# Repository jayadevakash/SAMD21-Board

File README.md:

# SAMD21-Board
Development Board Powered by SAMD21 Micro-controller. Project Credit: IoT Hive

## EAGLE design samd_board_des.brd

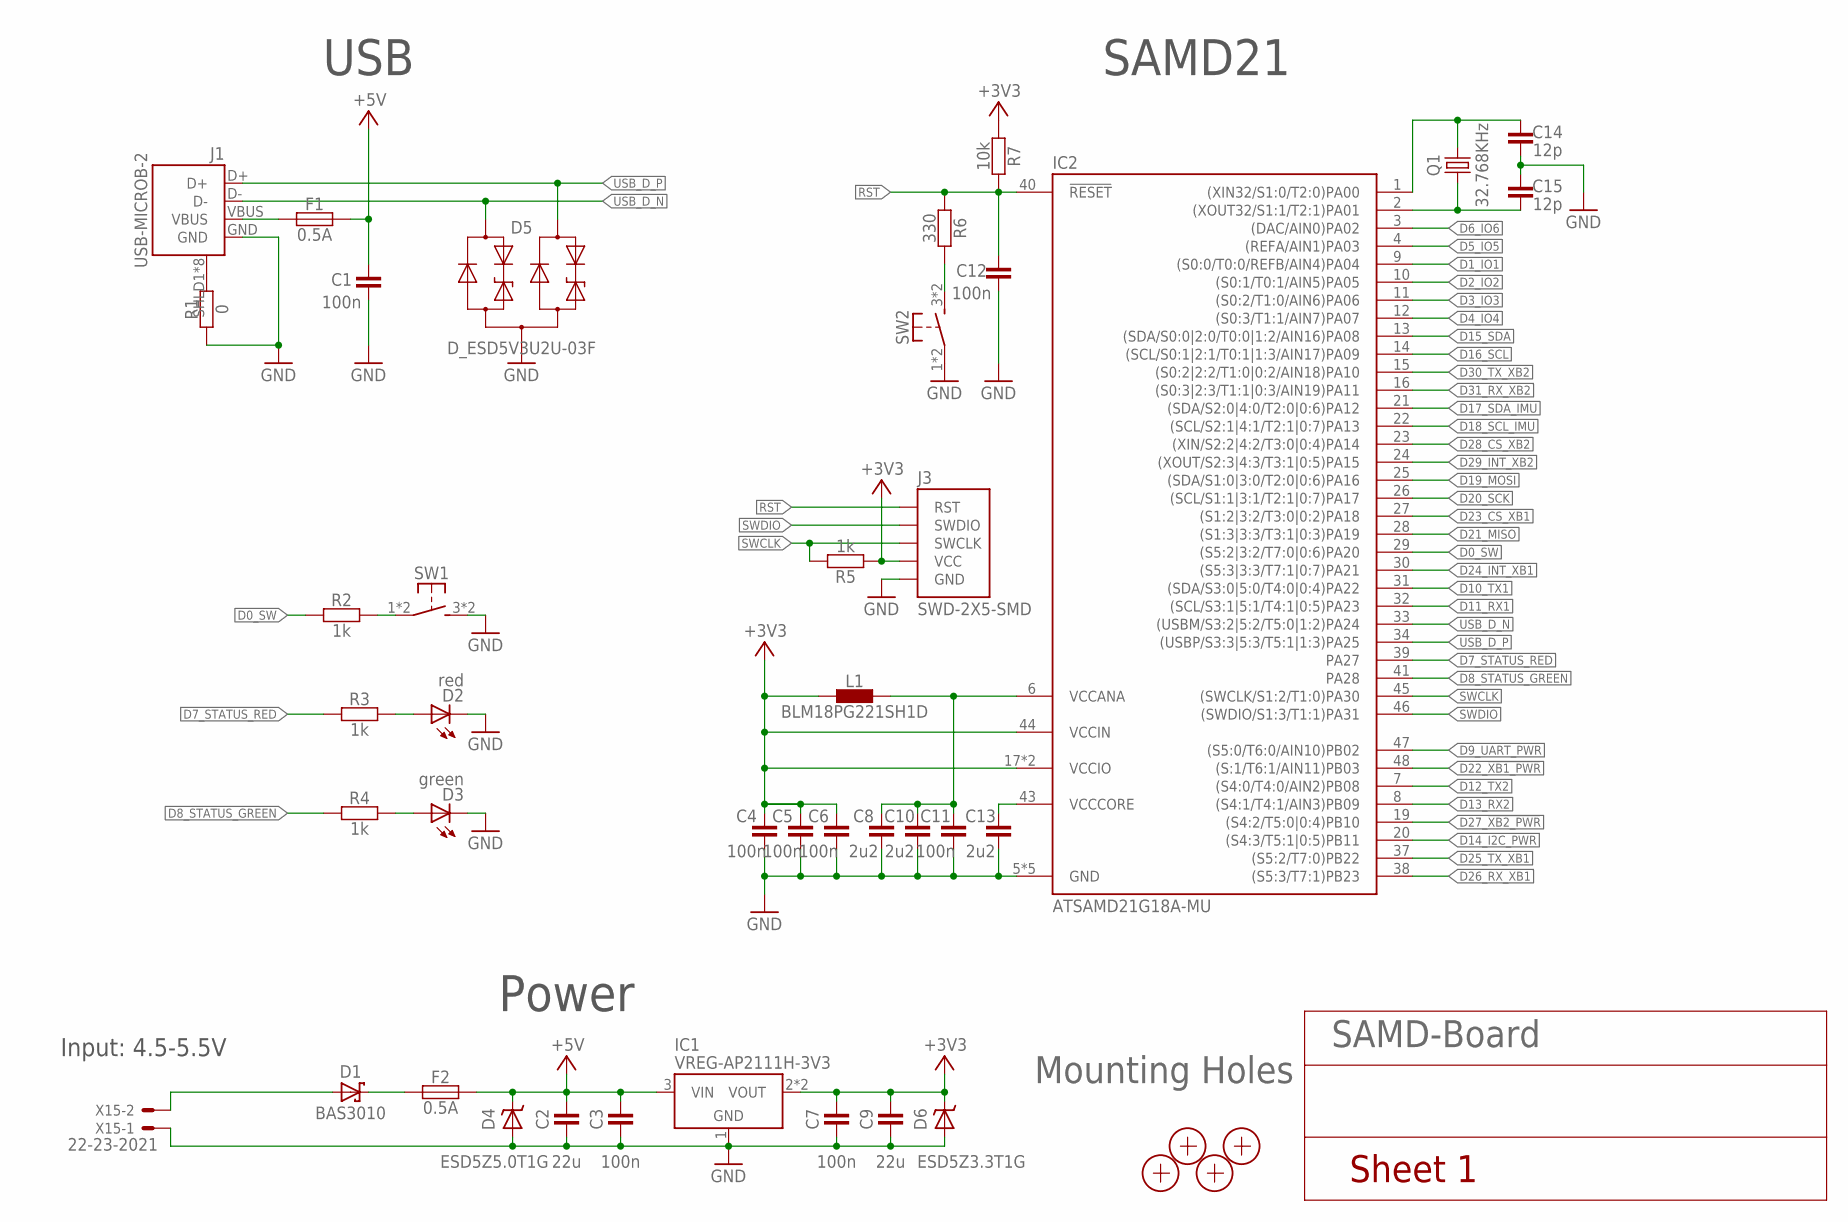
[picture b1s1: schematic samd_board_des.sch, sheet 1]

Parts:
C1, C3, C4, C5, C6, C7, C11, C12: 100n; C0402
C2, C9: 22u; C0805
C8, C10, C13: 2u2; C0402
C14, C15: 12p; C0402
D1: BAS3010; SOD323
D2: red; C0603
D3: green; C0603
D4: ESD5Z5.0T1G; SOD523
D5: D_ESD5V3U2U-03F; SOT723
D6: ESD5Z3.3T1G; SOD523
F1, F2: 0.5A; C0805
IC1: VREG-AP2111H-3V3; SOT223
IC2: ATSAMD21G18A-MU; QFN48-PAD
J1: USB-MICROB-2; USB-MICROB-10118194
J3: SWD-2X5-SMD; SWD-2X5_SMD
L1: BLM18PG221SH1D; C0603
Q1: 32.768KHz; CRYSTAL_ZM315
R1: 0; C0402
R2, R3, R4, R5: 1k; C0402
R6: 330; C0402
R7: 10k; C0402
SW1: PTS645SH50SMTR92-Grey; SW6X6_SMD
SW2: PTS645SK50SMTR92-Red; SW6X6_SMD
X1, X2, X3, X4: PASSER-07; PASSER_07MM
X15: 22-23-2021

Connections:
+3V3: C4.2, C5.2, C6.2, C7.2, C9.2, D6.C, IC1.2 (VOUT), IC1.4 (VOUT), IC2.17 (VCCIO), IC2.36 (VCCIO), IC2.44 (VCCIN), J3.VCC, L1.1, R5.1, R7.1; also elsewhere on the board
+5V: C1.2, C2.2, C3.2, D4.C, F1.2, F2.2, IC1.3 (VIN); also elsewhere on the board
D0_SW: IC2.29 ((S5:2|3:2/T7:0|0:6)PA20), R2.1
D1_IO1: IC2.9 ((S0:0/T0:0/REFB/AIN4)PA04); also elsewhere on the board
D2_IO2: IC2.10 ((S0:1/T0:1/AIN5)PA05); also elsewhere on the board
D3_IO3: IC2.11 ((S0:2/T1:0/AIN6)PA06); also elsewhere on the board
D4_IO4: IC2.12 ((S0:3/T1:1/AIN7)PA07); also elsewhere on the board
D5_IO5: IC2.4 ((REFA/AIN1)PA03); also elsewhere on the board
D6_IO6: IC2.3 ((DAC/AIN0)PA02); also elsewhere on the board
D7_STATUS_RED: IC2.39 (PA27), R3.1
D8_STATUS_GREEN: IC2.41 (PA28), R4.1
D9_UART_PWR: IC2.47 ((S5:0/T6:0/AIN10)PB02); also elsewhere on the board
D10_TX1: IC2.31 ((SDA/S3:0|5:0/T4:0|0:4)PA22); also elsewhere on the board
D11_RX1: IC2.32 ((SCL/S3:1|5:1/T4:1|0:5)PA23); also elsewhere on the board
D12_TX2: IC2.7 ((S4:0/T4:0/AIN2)PB08); also elsewhere on the board
D13_RX2: IC2.8 ((S4:1/T4:1/AIN3)PB09); also elsewhere on the board
D14_I2C_PWR: IC2.20 ((S4:3/T5:1|0:5)PB11); also elsewhere on the board
D15_SDA: IC2.13 ((SDA/S0:0|2:0/T0:0|1:2/AIN16)PA08); also elsewhere on the board
D16_SCL: IC2.14 ((SCL/S0:1|2:1/T0:1|1:3/AIN17)PA09); also elsewhere on the board
D17_SDA_IMU: IC2.21 ((SDA/S2:0|4:0/T2:0|0:6)PA12); also elsewhere on the board
D18_SCL_IMU: IC2.22 ((SCL/S2:1|4:1/T2:1|0:7)PA13); also elsewhere on the board
D19_MOSI: IC2.25 ((SDA/S1:0|3:0/T2:0|0:6)PA16); also elsewhere on the board
D20_SCK: IC2.26 ((SCL/S1:1|3:1/T2:1|0:7)PA17); also elsewhere on the board
D21_MISO: IC2.28 ((S1:3|3:3/T3:1|0:3)PA19); also elsewhere on the board
D22_!XB1_PWR: IC2.48 ((S:1/T6:1/AIN11)PB03); also elsewhere on the board
D23_CS_XB1: IC2.27 ((S1:2|3:2/T3:0|0:2)PA18); also elsewhere on the board
D24_INT_XB1: IC2.30 ((S5:3|3:3/T7:1|0:7)PA21); also elsewhere on the board
D25_TX_XB1: IC2.37 ((S5:2/T7:0)PB22); also elsewhere on the board
D26_RX_XB1: IC2.38 ((S5:3/T7:1)PB23); also elsewhere on the board
D27_!XB2_PWR: IC2.19 ((S4:2/T5:0|0:4)PB10); also elsewhere on the board
D28_CS_XB2: IC2.23 ((XIN/S2:2|4:2/T3:0|0:4)PA14); also elsewhere on the board
D29_INT_XB2: IC2.24 ((XOUT/S2:3|4:3/T3:1|0:5)PA15); also elsewhere on the board
D30_TX_XB2: IC2.15 ((S0:2|2:2/T1:0|0:2/AIN18)PA10); also elsewhere on the board
D31_RX_XB2: IC2.16 ((S0:3|2:3/T1:1|0:3/AIN19)PA11); also elsewhere on the board
GND: C1.1, C2.1, C3.1, C4.1, C5.1, C6.1, C7.1, C8.1, C9.1, C10.1, C11.1, C12.1, C13.1, C14.2, C15.1, D2.C, D3.C, D4.A, D5.3 (A), D6.A, IC1.1 (GND), IC2.5 (GND), IC2.18 (GND), IC2.35 (GND), IC2.42 (GND), IC2.TP (GND), J1.GND, J3.GND@1 (GND), J3.GND@2 (GND), J3.GND@3 (GND), R1.1, SW1.3 (S1), SW1.4 (S1), SW2.1, SW2.2 (P1), X15.1; also elsewhere on the board
unnamed: C14.1, IC2.1 ((XIN32/S1:0/T2:0)PA00), Q1.2
unnamed: C15.2, IC2.2 ((XOUT32/S1:1/T2:1)PA01), Q1.1
unnamed: D2.A, R3.2
unnamed: D3.A, R4.2
unnamed: R6.2, SW2.3 (S1), SW2.4 (S1)
RST: C12.2, IC2.40 (!RESET), J3.RST, R6.1, R7.2
SHLD: J1.SHLD1 (SHIELD), J1.SHLD2 (SHIELD), J1.SHLD3 (SHIELD), J1.SHLD4 (SHIELD), J1.SHLD5 (SHIELD), J1.SHLD6 (SHIELD), J1.SHLD7 (SHIELD), J1.SHLD8 (SHIELD), R1.2
SW: R2.2, SW1.1, SW1.2 (P1)
SWCLK: IC2.45 ((SWCLK/S1:2/T1:0)PA30), J3.SWCLK, R5.2
SWDIO: IC2.46 ((SWDIO/S1:3/T1:1)PA31), J3.SWDIO
USB_D_N: D5.1 (C1), IC2.33 ((USBM/S3:2|5:2/T5:0|1:2)PA24), J1.D-
USB_D_P: D5.2 (C2), IC2.34 ((USBP/S3:3|5:3/T5:1|1:3)PA25), J1.D+
V5V: D1.C, F2.1
VBUS: F1.1, J1.VBUS
VCCANA: C8.2, C10.2, C11.2, IC2.6 (VCCANA), L1.2
VCCCORE: C13.2, IC2.43 (VCCCORE)
VIN: D1.A, X15.2

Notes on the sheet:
USB
SAMD21
Power
Input: 4.5-5.5V
SAMD-Board
Sheet 1
Mounting Holes

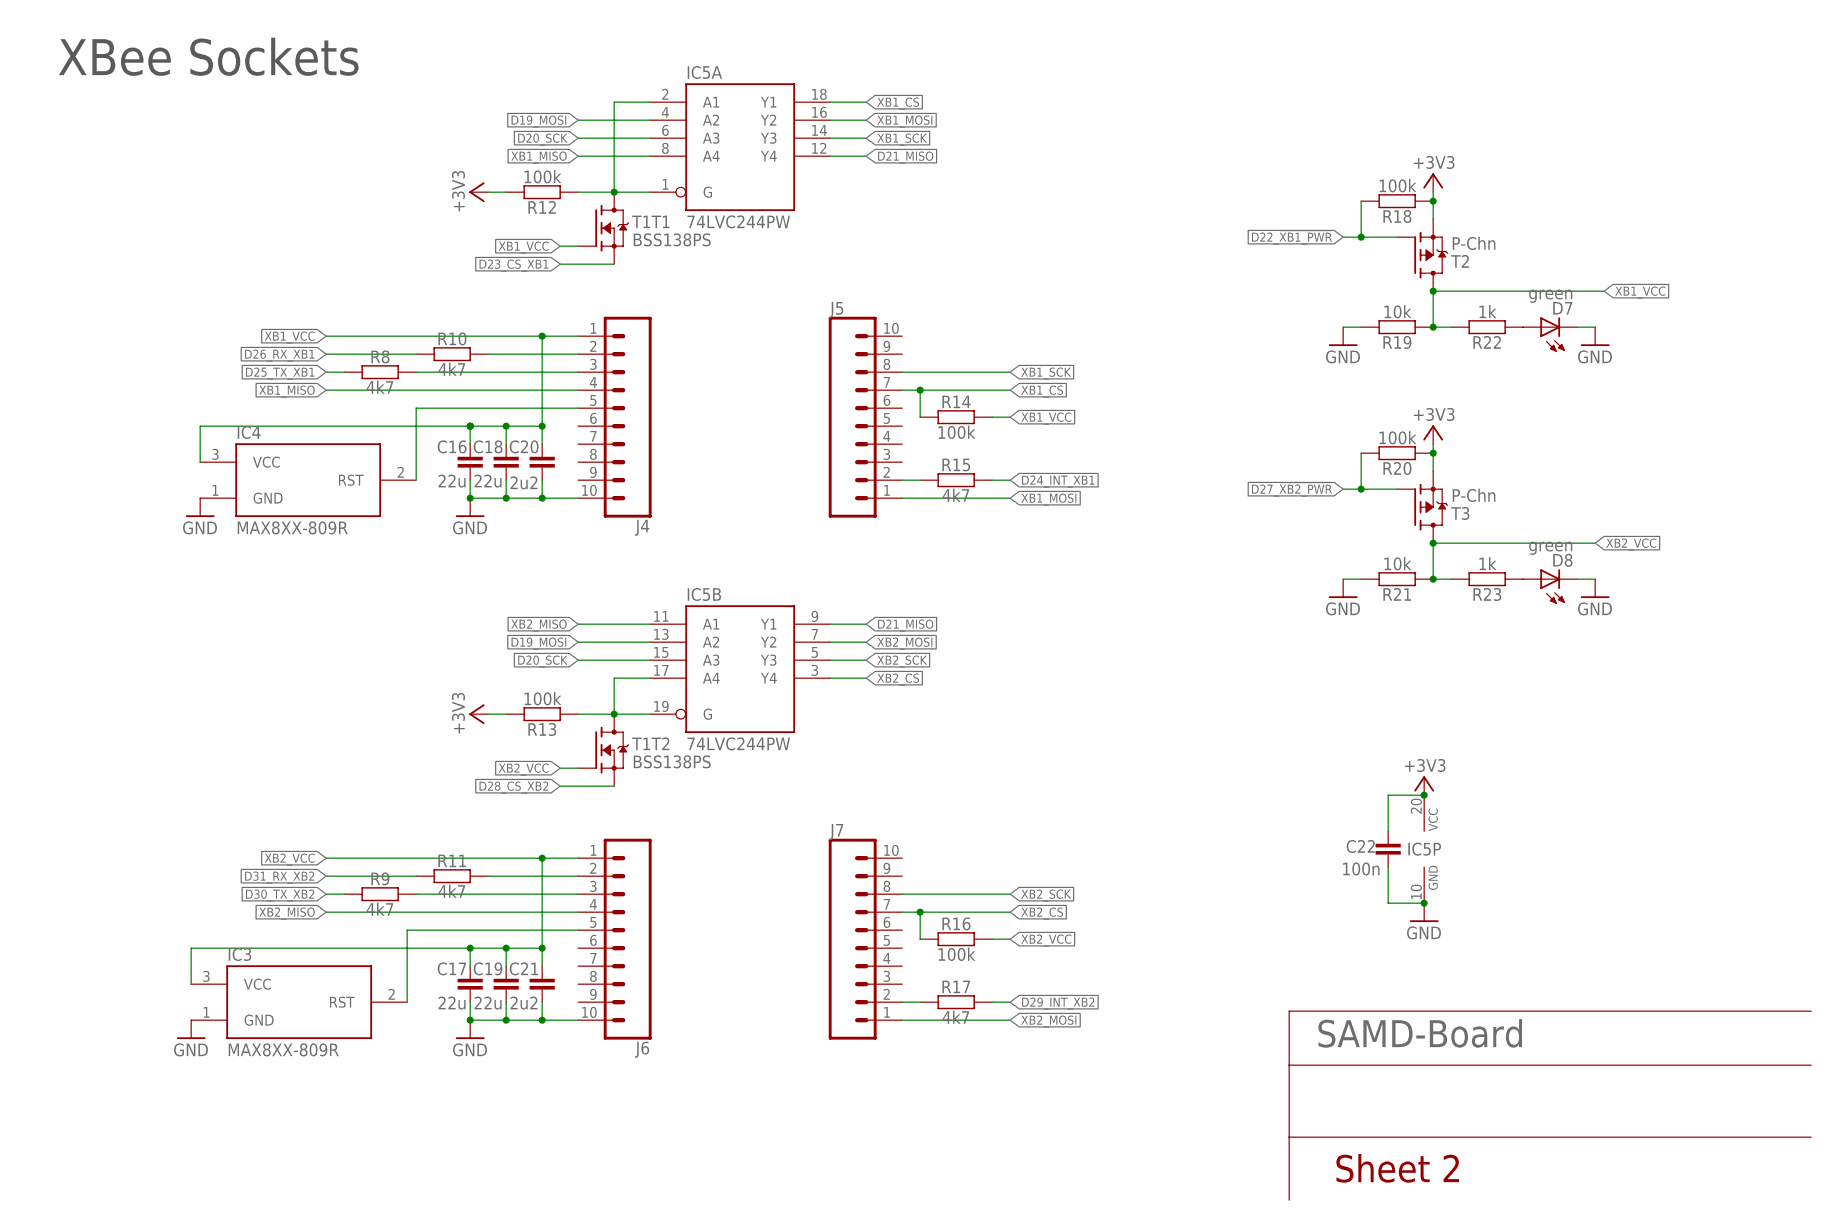
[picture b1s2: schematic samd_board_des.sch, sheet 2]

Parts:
C16, C17, C18, C19: 22u; C0805
C20, C21: 2u2; C0402
C22: 100n; C0402
D7, D8: green; C0603
IC3, IC4: MAX8XX-809R; SOT23
IC5: 74LVC244PW; TSSOP20
J4, J5, J6, J7: CONN_102MM; 1X10-2MM
R8, R9, R10, R11, R15, R17: 4k7; C0402
R12, R13, R14, R16, R18, R20: 100k; C0402
R19, R21: 10k; C0402
R22, R23: 1k; C0402
T1: BSS138PS; SOT363
T2, T3: P-Chn; SOT23

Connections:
+3V3: C22.2, IC5.20 (VCC), R12.2, R13.2, R18.1, R20.1, T2.2 (S), T3.2 (S); also elsewhere on the board
D19_MOSI: IC5.4 (A2), IC5.13 (A2); also elsewhere on the board
D20_SCK: IC5.6 (A3), IC5.15 (A3); also elsewhere on the board
D21_MISO: IC5.9 (Y1), IC5.12 (Y4); also elsewhere on the board
D22_!XB1_PWR: R18.2, T2.1 (G); also elsewhere on the board
D23_CS_XB1: T1.1 (S); also elsewhere on the board
D24_INT_XB1: R15.2; also elsewhere on the board
D25_TX_XB1: R8.1; also elsewhere on the board
D26_RX_XB1: R10.1; also elsewhere on the board
D27_!XB2_PWR: R20.2, T3.1 (G); also elsewhere on the board
D28_CS_XB2: T1.4 (S); also elsewhere on the board
D29_INT_XB2: R17.2; also elsewhere on the board
D30_TX_XB2: R9.1; also elsewhere on the board
D31_RX_XB2: R11.1; also elsewhere on the board
GND: C16.1, C17.1, C18.1, C19.1, C20.1, C21.1, C22.1, D7.C, D8.C, IC3.1 (GND), IC4.1 (GND), IC5.10 (GND), J4.10, J6.10, R19.2, R21.2; also elsewhere on the board
MCU_CS_XBEE1: IC5.1 (G), IC5.2 (A1), R12.1, T1.6 (D)
MCU_CS_XBEE2: IC5.17 (A4), IC5.19 (G), R13.1, T1.3 (D)
unnamed: D7.A, R22.1
unnamed: D8.A, R23.1
RST_XB1: IC4.2 (RST), J4.5
RST_XB2: IC3.2 (RST), J6.5
XB1_CS: IC5.18 (Y1), J5.7, R14.1
XB1_MISO: IC5.8 (A4), J4.4
XB1_MOSI: IC5.16 (Y2), J5.1
XB1_RX: J4.3, R8.2
XB1_SCK: IC5.14 (Y3), J5.8
XB1_TX: J4.2, R10.2
XB1_VCC: C16.2, C18.2, C20.2, IC4.3 (VCC), J4.1, R14.2, R19.1, R22.2, T1.2 (G), T2.3 (D)
XB2_CS: IC5.3 (Y4), J7.7, R16.1
XB2_MISO: IC5.11 (A1), J6.4
XB2_MOSI: IC5.7 (Y2), J7.1
XB2_RX: J6.3, R9.2
XB2_SCK: IC5.5 (Y3), J7.8
XB2_TX: J6.2, R11.2
XB2_VCC: C17.2, C19.2, C21.2, IC3.3 (VCC), J6.1, R16.2, R21.1, R23.2, T1.5 (G), T3.3 (D)
XBEE1_CTS/IRQ: J5.2, R15.1
XBEE2_CTS/IRQ: J7.2, R17.1

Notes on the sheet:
XBee Sockets
SAMD-Board
Sheet 2

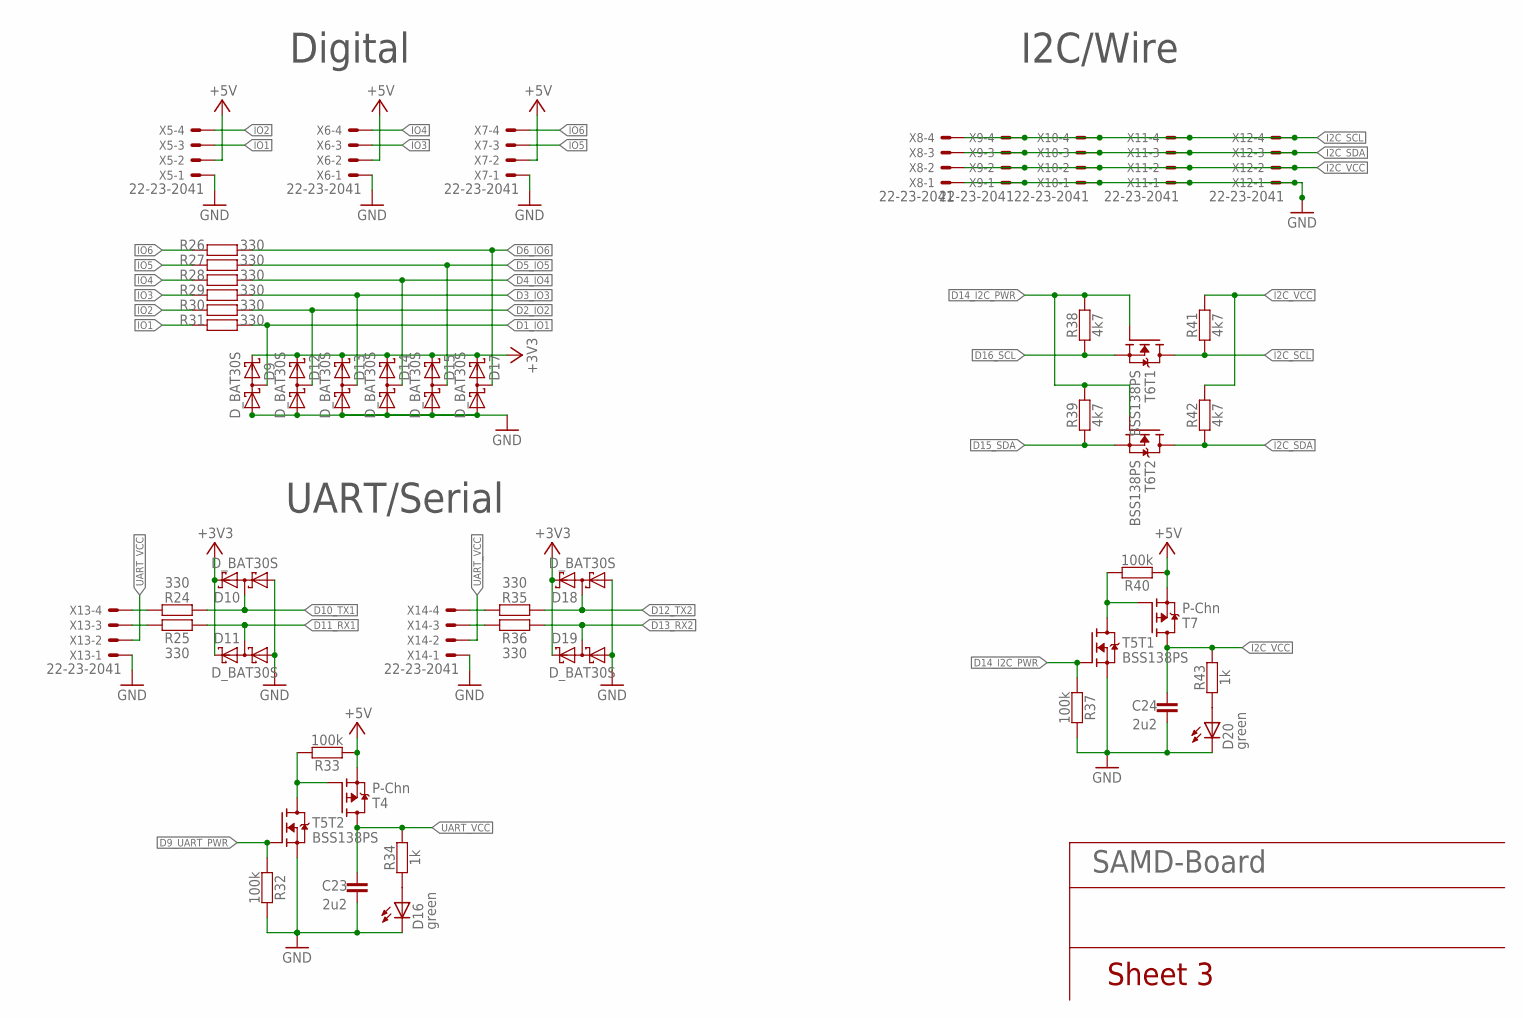
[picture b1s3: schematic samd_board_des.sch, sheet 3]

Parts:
C23, C24: 2u2; C0402
D9, D10, D11, D12, D13, D14, D15, D17, D18, D19: D_BAT30S; SOT323
D16, D20: green; C0603
R24, R25, R26, R27, R28, R29, R30, R31, R35, R36: 330; C0402
R32, R33, R37, R40: 100k; C0402
R34, R43: 1k; C0402
R38, R39, R41, R42: 4k7; C0402
T4, T7: P-Chn; SOT23
T5, T6: BSS138PS; SOT363
X5, X6, X7, X8, X9, X10, X11, X12, X13, X14: 22-23-2041

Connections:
!I2C_POWER: R40.2, T5.6 (D), T7.1 (G)
!UART_POWER: R33.2, T4.1 (G), T5.3 (D)
+3V3: D9.2 (C), D10.2 (C), D11.2 (C), D12.2 (C), D13.2 (C), D14.2 (C), D15.2 (C), D17.2 (C), D18.2 (C), D19.2 (C); also elsewhere on the board
+5V: R33.1, R40.1, T4.2 (S), T7.2 (S), X5.2, X6.2, X7.2; also elsewhere on the board
D1_IO1: D9.3 (CA), R31.1; also elsewhere on the board
D2_IO2: D12.3 (CA), R30.1; also elsewhere on the board
D3_IO3: D13.3 (CA), R29.1; also elsewhere on the board
D4_IO4: D14.3 (CA), R28.1; also elsewhere on the board
D5_IO5: D15.3 (CA), R27.1; also elsewhere on the board
D6_IO6: D17.3 (CA), R26.1; also elsewhere on the board
D9_UART_PWR: R32.1, T5.5 (G); also elsewhere on the board
D10_TX1: D10.3 (CA), R24.1; also elsewhere on the board
D11_RX1: D11.3 (CA), R25.1; also elsewhere on the board
D12_TX2: D18.3 (CA), R35.1; also elsewhere on the board
D13_RX2: D19.3 (CA), R36.1; also elsewhere on the board
D14_I2C_PWR: R37.1, R38.2, R39.2, T5.2 (G), T6.2 (G), T6.5 (G); also elsewhere on the board
D15_SDA: R39.1, T6.4 (S); also elsewhere on the board
D16_SCL: R38.1, T6.1 (S); also elsewhere on the board
GND: C23.1, C24.1, D9.1 (A), D10.1 (A), D11.1 (A), D12.1 (A), D13.1 (A), D14.1 (A), D15.1 (A), D16.C, D17.1 (A), D18.1 (A), D19.1 (A), D20.C, R32.2, R37.2, T5.1 (S), T5.4 (S), X5.1, X6.1, X7.1, X8.1, X9.1, X10.1, X11.1, X12.1, X13.1, X14.1; also elsewhere on the board
I2C_SCL: R41.1, T6.6 (D), X8.4, X9.4, X10.4, X11.4, X12.4
I2C_SDA: R42.1, T6.3 (D), X8.3, X9.3, X10.3, X11.3, X12.3
I2C_VCC: C24.2, R41.2, R42.2, R43.2, T7.3 (D), X8.2, X9.2, X10.2, X11.2, X12.2
IO1: R31.2, X5.3
IO2: R30.2, X5.4
IO3: R29.2, X6.3
IO4: R28.2, X6.4
IO5: R27.2, X7.3
IO6: R26.2, X7.4
unnamed: D20.A, R43.1
unnamed: D16.A, R34.1
UART_RX1: R25.2, X13.3
UART_RX2: R36.2, X14.3
UART_TX1: R24.2, X13.4
UART_TX2: R35.2, X14.4
UART_VCC: C23.2, R34.2, T4.3 (D), X13.2, X14.2

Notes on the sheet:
Digital
I2C/Wire
UART/Serial
SAMD-Board
Sheet 3

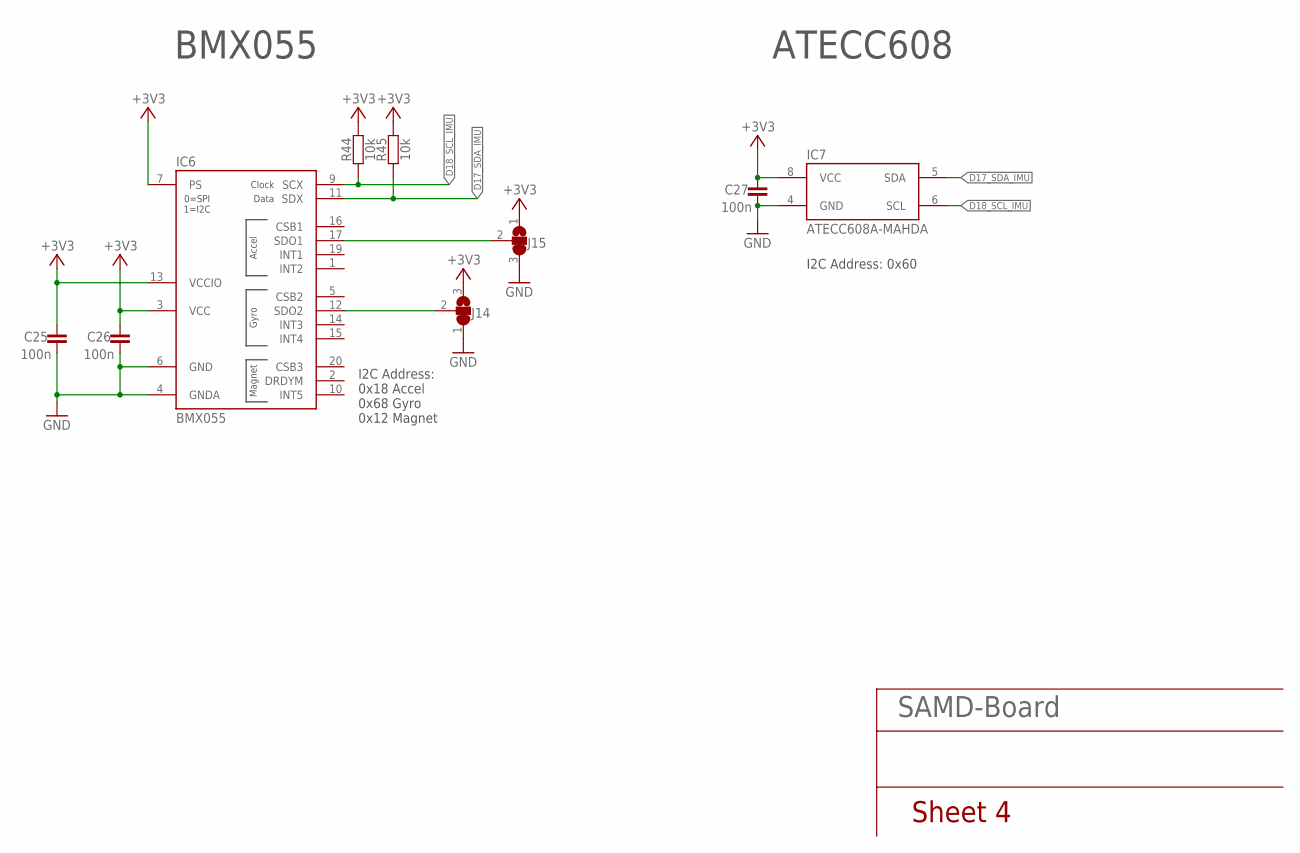
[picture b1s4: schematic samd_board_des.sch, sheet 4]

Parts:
C25, C26, C27: 100n; C0402
IC6: BMX055
IC7: ATECC608A-MAHDA; UDFN8
J14, J15: JUMPER3-0402
R44, R45: 10k; C0402

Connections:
+3V3: C25.2, C26.2, C27.2, IC6.3 (VCC), IC6.7 (PS), IC6.13 (VCCIO), IC7.8 (VCC), J14.3, J15.1, R44.2, R45.2; also elsewhere on the board
D17_SDA_IMU: IC6.11 (SDX), IC7.5 (SDA), R45.1; also elsewhere on the board
D18_SCL_IMU: IC6.9 (SCX), IC7.6 (SCL), R44.1; also elsewhere on the board
GND: C25.1, C26.1, C27.1, IC6.4 (GNDA), IC6.6 (GND), IC7.4 (GND), J14.1, J15.3; also elsewhere on the board
SDO1: IC6.17 (SDO1), J15.2
SDO2: IC6.12 (SDO2), J14.2

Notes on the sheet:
I2C Address: 0x18 Accel 0x68 Gyro 0x12 Magnet
I2C Address: 0x60
BMX055
ATECC608
SAMD-Board
Sheet 4

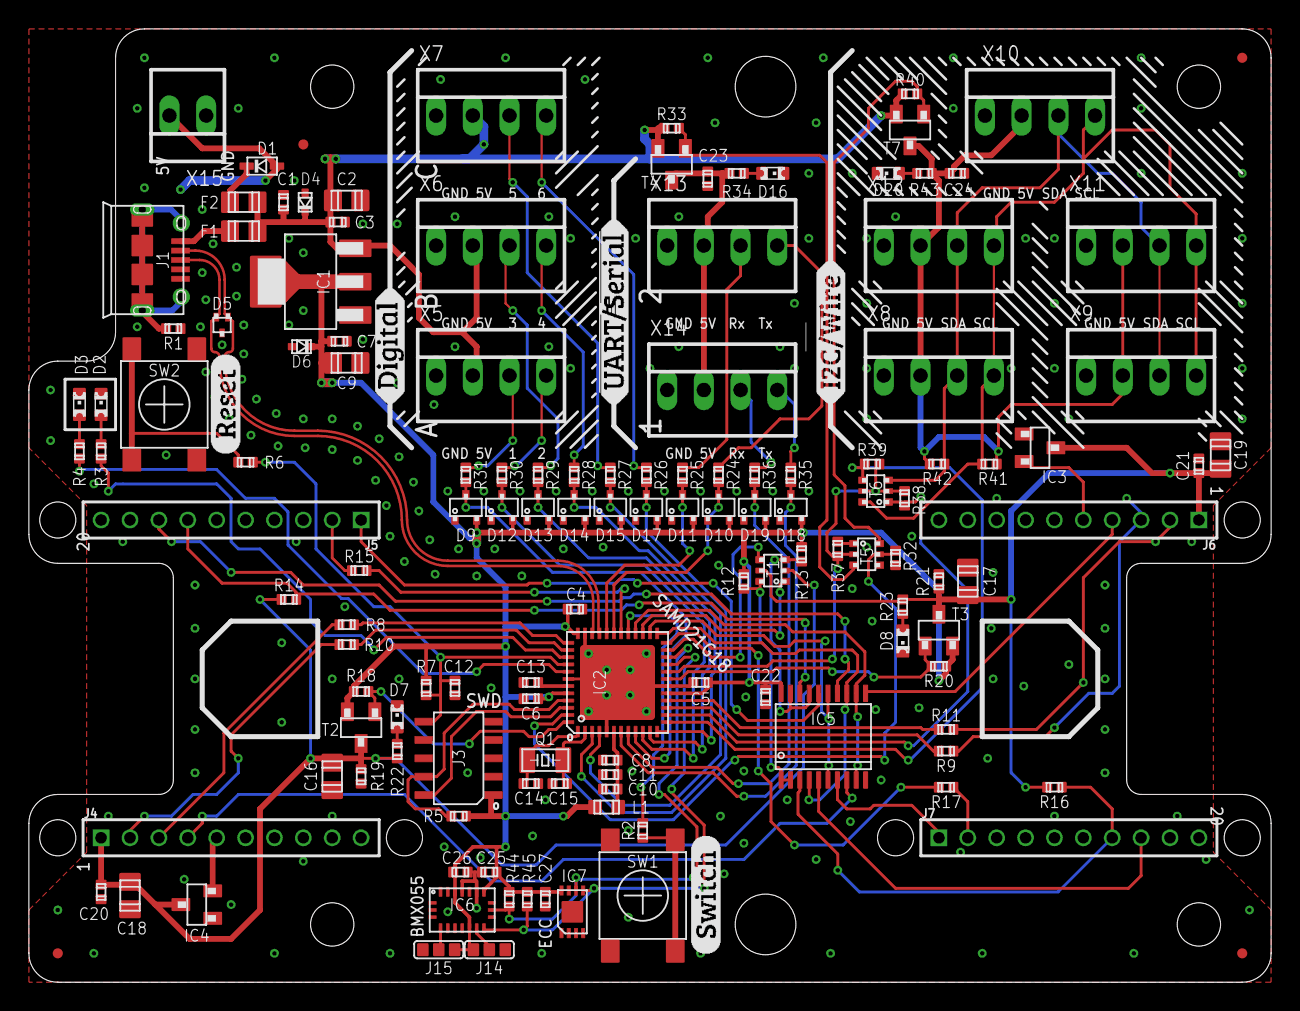
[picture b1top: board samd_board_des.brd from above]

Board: 2 copper layers, 86.0 x 66.0 mm, 135 parts (0 on the bottom side), 94 nets.

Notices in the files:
parts and their libraries:
SparkFun-Connectors: Licensing: Creative Commons ShareAlike 4.0 International - https://creativecommons.org/licenses/by-sa/4.0
